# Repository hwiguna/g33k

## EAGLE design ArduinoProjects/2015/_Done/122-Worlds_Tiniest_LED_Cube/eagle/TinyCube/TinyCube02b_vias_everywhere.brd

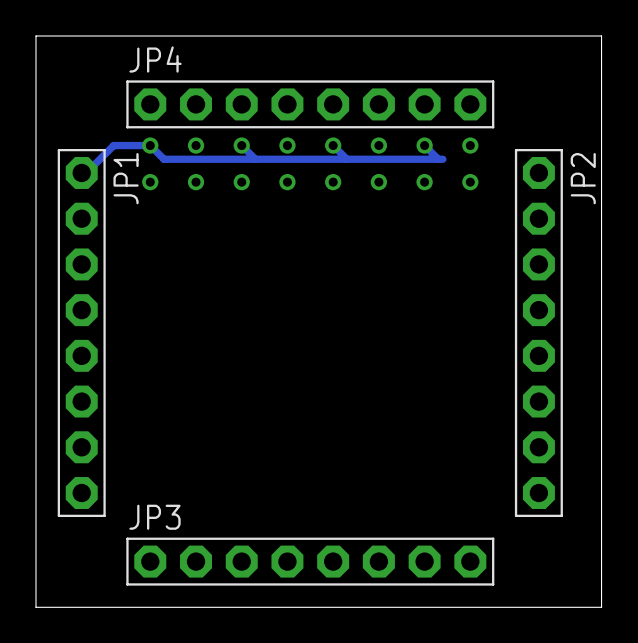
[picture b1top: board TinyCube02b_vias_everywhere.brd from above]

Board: 2 copper layers, 31.4 x 31.7 mm, 4 parts (0 on the bottom side), 8 nets.

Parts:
JP1, JP2, JP3, JP4: 1X08-BIG

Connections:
unnamed: JP1.2, JP2.2
unnamed: JP1.5, JP2.5
unnamed: JP1.1, JP2.1
unnamed: JP1.3, JP2.3
unnamed: JP1.4, JP2.4
unnamed: JP1.6, JP2.6
unnamed: JP1.7, JP2.7
unnamed: JP1.8, JP2.8

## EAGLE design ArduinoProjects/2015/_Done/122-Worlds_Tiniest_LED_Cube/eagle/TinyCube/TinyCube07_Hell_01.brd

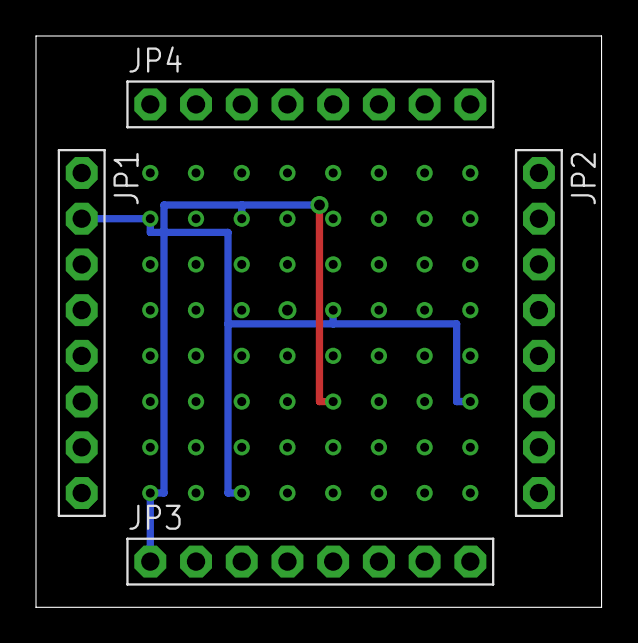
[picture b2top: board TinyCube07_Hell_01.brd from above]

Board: 2 copper layers, 31.4 x 31.7 mm, 4 parts (0 on the bottom side), 16 nets.

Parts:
JP1, JP2, JP3, JP4: 1X08-BIG

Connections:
unnamed: JP1.2, JP2.2
unnamed: JP1.5, JP2.5
unnamed: JP1.1, JP2.1
unnamed: JP1.3, JP2.3
unnamed: JP1.4, JP2.4
unnamed: JP1.6, JP2.6
unnamed: JP1.7, JP2.7
unnamed: JP1.8, JP2.8
unnamed: JP3.1, JP4.1
unnamed: JP3.2, JP4.2
unnamed: JP3.3, JP4.3
unnamed: JP3.4, JP4.4
unnamed: JP3.5, JP4.5
unnamed: JP3.6, JP4.6
unnamed: JP3.7, JP4.7
unnamed: JP3.8, JP4.8

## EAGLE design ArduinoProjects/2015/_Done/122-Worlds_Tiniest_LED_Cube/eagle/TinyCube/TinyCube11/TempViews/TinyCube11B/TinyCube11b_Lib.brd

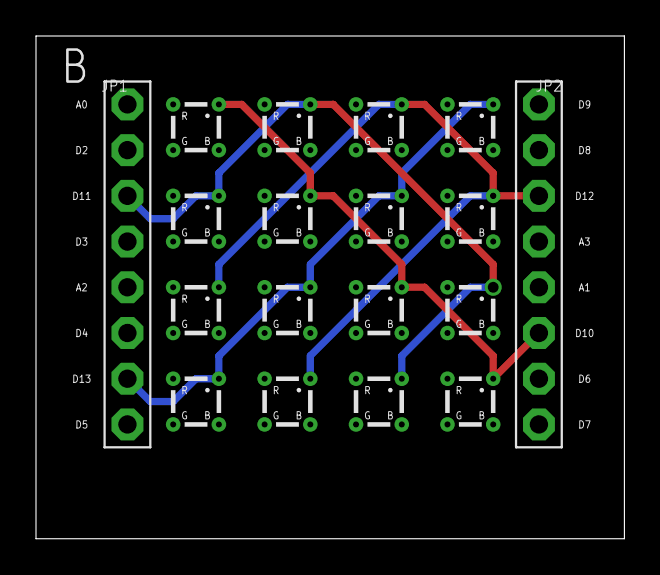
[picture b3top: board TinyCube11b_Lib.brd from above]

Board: 2 copper layers, 32.7 x 27.9 mm, 18 parts (0 on the bottom side), 4 nets.

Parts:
JP1, JP2: 1X08-BIG
U$1, U$2, U$3, U$4, U$5, U$6, U$7, U$8, U$9, U$10, U$11, U$12, U$13, U$14, U$15, U$16: PILLAR; 10MIL

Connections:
unnamed: JP1.3, U$2.+, U$5.+, U$12.+, U$15.+
unnamed: JP1.7, U$4.+, U$7.+, U$10.+, U$13.+
unnamed: JP2.6, U$1.+, U$6.+, U$11.+, U$16.+
unnamed: JP2.3, U$3.+, U$8.+, U$9.+, U$14.+
